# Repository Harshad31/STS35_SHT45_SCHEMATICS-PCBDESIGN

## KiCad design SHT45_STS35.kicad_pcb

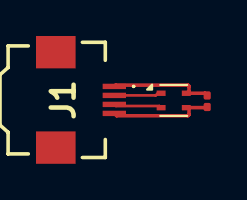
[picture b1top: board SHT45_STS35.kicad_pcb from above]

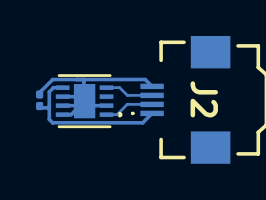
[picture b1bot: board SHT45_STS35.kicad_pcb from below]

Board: 2 copper layers, 6 parts (3 on the bottom side), 8 nets.

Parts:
C1, C2: 100nF; C_0201_0603Metric
J1, J2: FFC2B35-04-T; FFC2B3504T
U1: SHT4x; Sensirion_DFN-4_1.5x1.5mm_P0.8mm_SHT4x_NoCentralPad
U2: STS35-DIS; STS3x-DIS_SEN

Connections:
/GND: U2.2 (ADDR), U2.6 (NRESET), U2.7 (R), U2.8 (VSS)
/SCL: J1.3, U1.2 (SCL)
/SCL0: J2.3, U2.4 (SCL)
/SDA: J1.2, U1.1 (SDA)
/SDA0: J2.2, U2.1 (SDA)
/VDD: C2.1, J1.4, U1.3 (VDD)
/VDD3.3: C1.1, J2.1, U2.5 (VDD)
GND: C1.2, C2.2, J1.1, J2.4, U1.4 (VSS), U2.9 (VSS)
